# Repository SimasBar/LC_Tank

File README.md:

# LC_Tank
Built a simple LC Tank circuit for funsies, works fine with 5V and 9V supplies, resonates up to 20Vpp.
Used rf inductors, could optimize more with proper power inductors. Also used another inductor as an antenna to drive an LED LOL.

# Schematic

# In action

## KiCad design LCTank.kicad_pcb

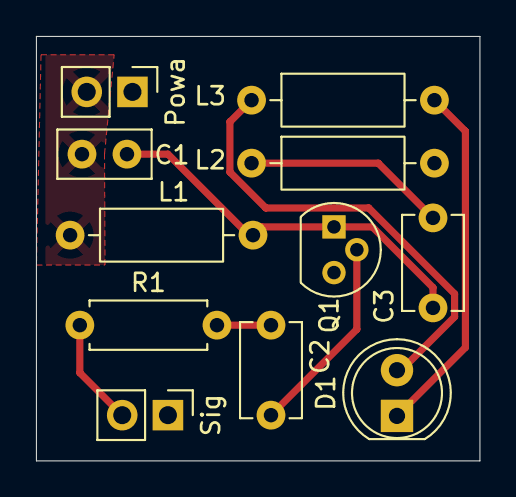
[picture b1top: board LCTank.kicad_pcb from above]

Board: 2 copper layers, 24.6 x 23.6 mm, 11 parts (0 on the bottom side), 9 nets.

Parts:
C1: 100n; C_Disc_D5.0mm_W2.5mm_P2.50mm
C2, C3: 100n; C_Disc_D5.1mm_W3.2mm_P5.00mm
D1: LED; LED_D5.0mm
L1, L2: 1m; L_Axial_L6.6mm_D2.7mm_P10.16mm_Horizontal_Vishay_IM-2
L3: 4.7m; L_Axial_L6.6mm_D2.7mm_P10.16mm_Horizontal_Vishay_IM-2
Powa: Conn_01x02; PinHeader_1x02_P2.54mm_Vertical
Q1: 2N2222A; TO-92
R1: 1k; R_Axial_DIN0207_L6.3mm_D2.5mm_P7.62mm_Horizontal
Sig: Conn_01x02; PinHeader_1x02_P2.54mm_Vertical

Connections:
+5V: C1.1, L1.1, Powa.2
GND: L2.2, Powa.1, Q1.3 (E), Sig.1
unnamed: C2.1, R1.2
unnamed: C3.2, L2.1
unnamed: D1.2 (A), L3.1
unnamed: D1.1 (K), L3.2
unnamed: C2.2, Q1.2 (B)
unnamed: C1.2, C3.1, L1.2, Q1.1 (C)
Signal: R1.1, Sig.2

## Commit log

2026-05-12 Hello world
2026-05-12 Whoops
2026-05-12 Added connectors and pcb
